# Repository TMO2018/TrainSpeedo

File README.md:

# TrainSpeedo
The project is based on the source:
https://dcc-arduino.weebly.com/scale-speedometer.html

This project is a "real size" speedometer for miniature trains, cars and anything you wish to measure.
It can calculate the speed of the object between 2 measuring points along the track (or road) by counting milliseconds between passages at the start and end gates. If you enter the distance between those gates (in dm) and the used scale (ex. H0 = 1:87) in to the Arduino, it will calculate the actual "real" speed of the object if it were on a 1:1 scale in the real world. This is a useful tool for measuring and calibrating the speed of your model trains on the layout, in order to be able to set and control their speed in the PC or central station for a realistic run on the tracks.

2 detectors are set up along the track, at a known distance (in dm) from each other. When a train runs by one of the detectors, the timer is started, the switch is auto-disabled (to eliminate double counts or other forms of interference) and only when the object passes by the other detector, will the timer be stopped and will the module calculate the speed based on time , distance and scale factors.

Due to the auto-disable fuction of the detectors, the system can calculate either LTR or RTL (left to right or right to left) moving objects with the same accuracy.

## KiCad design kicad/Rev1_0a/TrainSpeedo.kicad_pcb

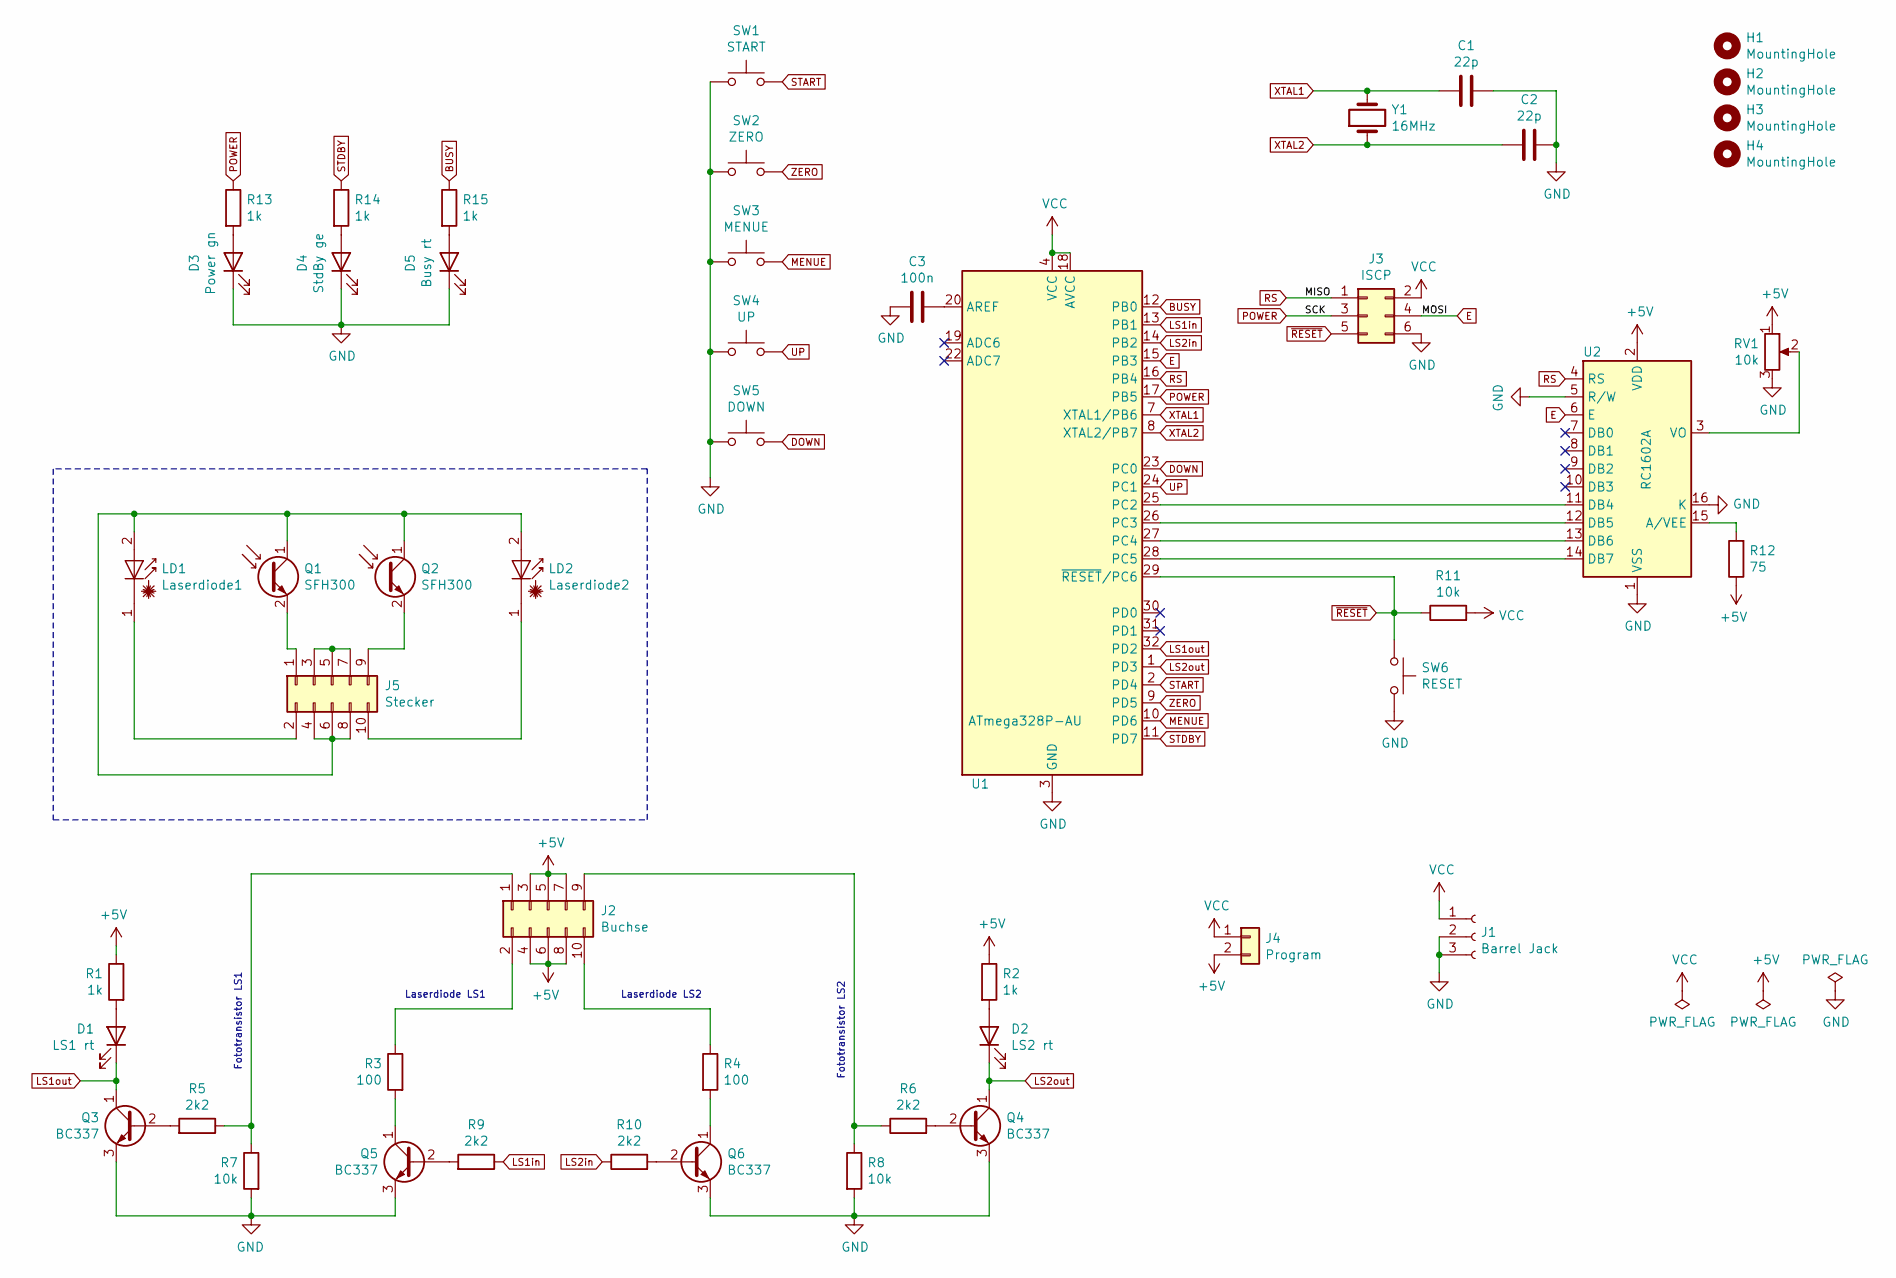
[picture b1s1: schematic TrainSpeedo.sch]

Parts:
C1, C2: 22p; C_0805_HandSoldering
C3: 100n; C_0805_HandSoldering
D1: LS1 rt; LED_D3.0mm
D2: LS2 rt; LED_D3.0mm
D3: Power gn; LED_D5.0mm
D4: StdBy ge; LED_D5.0mm
D5: Busy rt; LED_D5.0mm
H1, H2, H3, H4: MountingHole; MountingHole_3.2mm_M3
J1: Barrel Jack; BARREL_JACK
J2: Buchse; Pin_Header_Straight_2x05_Pitch2.54mm
J3: ISCP; Pin_Header_Straight_2x03_Pitch2.54mm
J4: Program; Pin_Header_Straight_1x02_Pitch2.54mm
J5: Stecker
LD1: Laserdiode1
LD2: Laserdiode2
Q1, Q2: SFH300
Q3, Q4, Q5, Q6: BC337; TO-92_Inline_Wide
R1, R2, R13, R14, R15: 1k; R_0805_HandSoldering
R3, R4: 100; R_0805_HandSoldering
R5, R6, R9, R10: 2k2; R_0805_HandSoldering
R7, R8, R11: 10k; R_0805_HandSoldering
R12: 75; R_0805_HandSoldering
RV1: 10k; Potentiometer_Triwood_RM-065
SW1: START; SW_PUSH_6mm
SW2: ZERO; SW_PUSH_6mm
SW3: MENUE; SW_PUSH_6mm
SW4: UP; SW_PUSH_6mm
SW5: DOWN; SW_PUSH_6mm
SW6: RESET; SW_PUSH_6mm
U1: ATmega328P-AU; TQFP-32_7x7mm_Pitch0.8mm
U2: RC1602A; WC1602A
Y1: 16MHz; Crystal_HC49-U_Vertical

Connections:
+5V: J2.3, J2.4, J2.5, J2.6, J2.7, J2.8, J4.2, R1.1, R2.1, R12.1, RV1.1, U2.2 (VDD)
BUSY: R15.1, U1.12 (PB0)
DOWN: SW5.2, U1.23 (PC0)
E: J3.4, U1.15 (PB3), U2.6 (E)
GND: C1.1, C2.1, C3.2, D3.1 (K), D4.1 (K), D5.1 (K), J1.2, J1.3, J3.6, Q3.3 (E), Q4.3 (E), Q5.3 (E), Q6.3 (E), R7.2, R8.2, RV1.3, SW1.1, SW2.1, SW3.1, SW4.1, SW5.1, SW6.2, U1.3 (GND), U1.5 (GND), U1.21 (GND), U2.1 (VSS), U2.5 (R/W), U2.16 (K)
LS1in: R9.1, U1.13 (PB1)
LS1out: D1.1 (K), Q3.1 (C), U1.32 (PD2)
LS2in: R10.1, U1.14 (PB2)
LS2out: D2.1 (K), Q4.1 (C), U1.1 (PD3)
MENUE: SW3.2, U1.10 (PD6)
unnamed: C3.1, U1.20 (AREF)
unnamed: D1.2 (A), R1.2
unnamed: D2.2 (A), R2.2
unnamed: D3.2 (A), R13.2
unnamed: D4.2 (A), R14.2
unnamed: D5.2 (A), R15.2
unnamed: J2.1, R5.1, R7.1
unnamed: J2.2, R3.1
unnamed: J2.9, R6.1, R8.1
unnamed: J2.10, R4.1
unnamed: J5.1, Q1.2 (E)
unnamed: J5.2, LD1.1 (K)
unnamed: J5.3, J5.5, J5.7
unnamed: J5.4, J5.6, J5.8, LD1.2 (A), LD2.2 (A), Q1.1 (C), Q2.1 (C)
unnamed: J5.9, Q2.2 (E)
unnamed: J5.10, LD2.1 (K)
unnamed: Q3.2 (B), R5.2
unnamed: Q4.2 (B), R6.2
unnamed: Q5.1 (C), R3.2
unnamed: Q5.2 (B), R9.2
unnamed: Q6.1 (C), R4.2
unnamed: Q6.2 (B), R10.2
unnamed: R12.2, U2.15 (A/VEE)
unnamed: RV1.2, U2.3 (VO)
unnamed: U1.25 (PC2), U2.11 (DB4)
unnamed: U1.26 (PC3), U2.12 (DB5)
unnamed: U1.27 (PC4), U2.13 (DB6)
unnamed: U1.28 (PC5), U2.14 (DB7)
POWER: J3.3, R13.1, U1.17 (PB5)
RS: J3.1, U1.16 (PB4), U2.4 (RS)
START: SW1.2, U1.2 (PD4)
STDBY: R14.1, U1.11 (PD7)
UP: SW4.2, U1.24 (PC1)
VCC: J1.1, J3.2, J4.1, R11.2, U1.4 (VCC), U1.6 (VCC), U1.18 (AVCC)
XTAL1: C1.2, U1.7 (XTAL1/PB6), Y1.2
XTAL2: C2.2, U1.8 (XTAL2/PB7), Y1.1
ZERO: SW2.2, U1.9 (PD5)
~RESET: J3.5, R11.1, SW6.1, U1.29 (~RESET~/PC6)

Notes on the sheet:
Fototransistor LS1
Fototransistor LS2
Laserdiode LS1
Laserdiode LS2

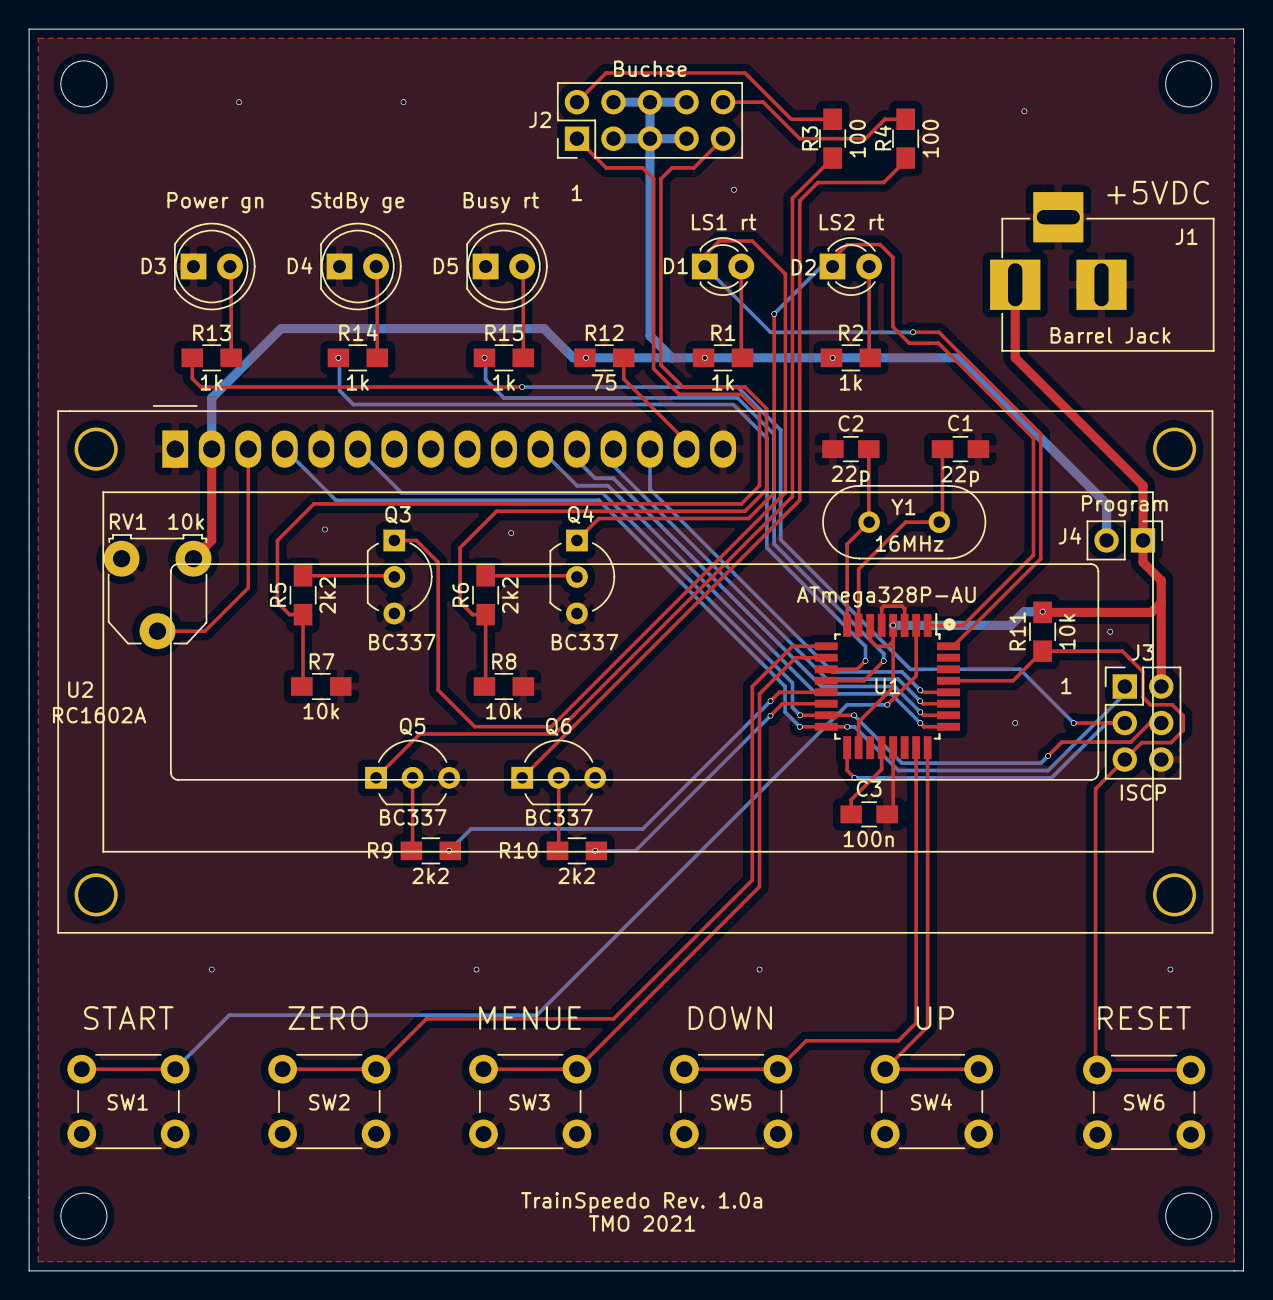
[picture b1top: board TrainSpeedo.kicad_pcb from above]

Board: 2 copper layers, 84.5 x 86.4 mm, 45 parts (0 on the bottom side), 42 nets.
